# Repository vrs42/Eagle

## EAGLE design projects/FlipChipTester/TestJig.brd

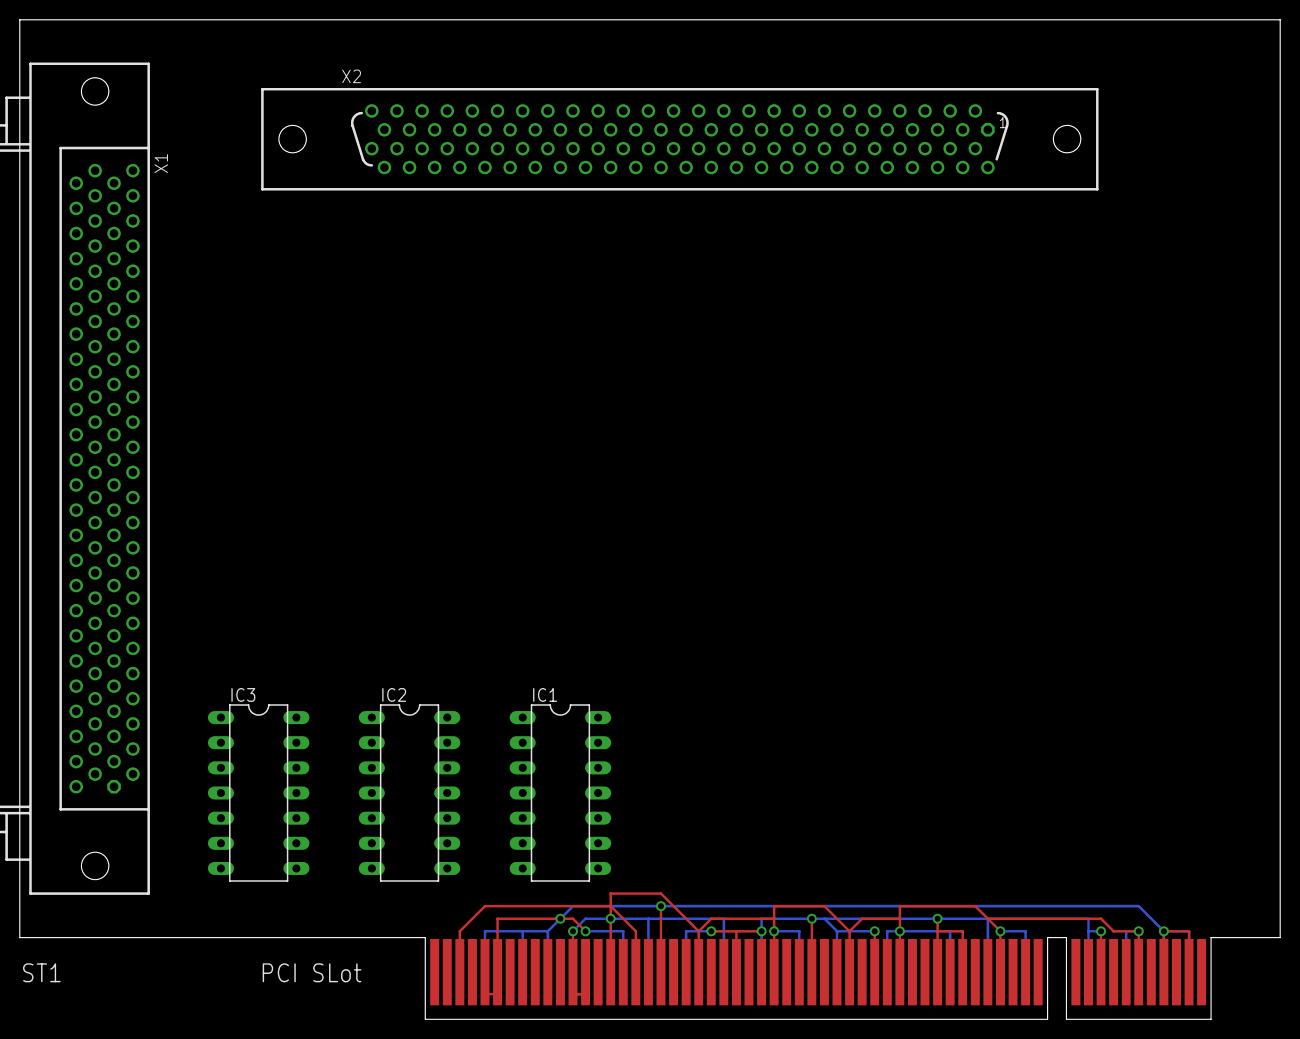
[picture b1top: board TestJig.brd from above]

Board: 2 copper layers, 127.3 x 101.0 mm, 6 parts (0 on the bottom side), 4 nets.

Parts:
IC1: 74125N; DIL14
IC2: 74126N; DIL14
IC3: 74LS63N; DIL14
ST1: PCI_BRD
X1: HFR100RA
X2: HXR100ST

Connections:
+3,3V: ST1.C25, ST1.C31, ST1.C36, ST1.C41, ST1.C43, ST1.C54, ST1.S21, ST1.S27, ST1.S33, ST1.S45, ST1.S53
+5V: ST1.C5, ST1.C6, ST1.C19, ST1.C59, ST1.C61, ST1.C62, ST1.S5, ST1.S8, ST1.S10, ST1.S16, ST1.S59, ST1.S61, ST1.S62
GND: IC1.7, IC2.7, IC3.7, ST1.C3, ST1.C12, ST1.C13, ST1.C15, ST1.C17, ST1.C22, ST1.C28, ST1.C34, ST1.C38, ST1.C46, ST1.C49, ST1.C57, ST1.S12, ST1.S13, ST1.S18, ST1.S24, ST1.S30, ST1.S37, ST1.S42, ST1.S48, ST1.S56
VCC: IC1.14, IC2.14, IC3.14

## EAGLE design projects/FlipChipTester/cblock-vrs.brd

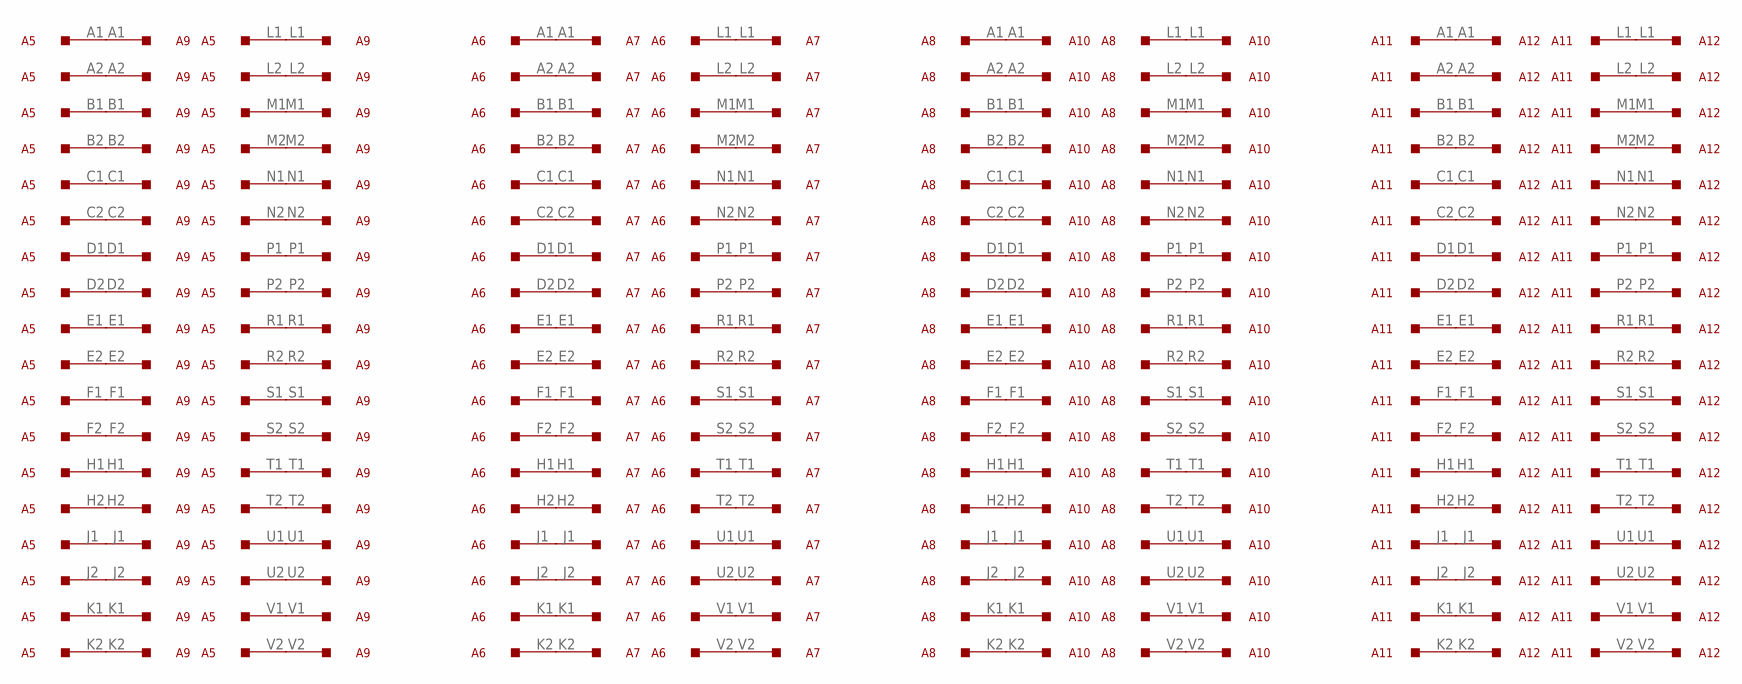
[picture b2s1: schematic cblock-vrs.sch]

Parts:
A5, A6, A7, A8, A9, A10, A11, A12: M916; H807

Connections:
unnamed: A5.L1, A9.L1
unnamed: A5.L2, A9.L2
unnamed: A5.M1, A9.M1
unnamed: A5.M2, A9.M2
unnamed: A5.N1, A9.N1
unnamed: A5.N2, A9.N2
unnamed: A5.P1, A9.P1
unnamed: A5.P2, A9.P2
unnamed: A5.R1, A9.R1
unnamed: A5.R2, A9.R2
unnamed: A5.S1, A9.S1
unnamed: A5.S2, A9.S2
unnamed: A5.T1, A9.T1
unnamed: A5.T2, A9.T2
unnamed: A5.U1, A9.U1
unnamed: A5.U2, A9.U2
unnamed: A5.V1, A9.V1
unnamed: A5.V2, A9.V2
unnamed: A5.A1, A9.A1
unnamed: A5.A2, A9.A2
unnamed: A5.B1, A9.B1
unnamed: A5.B2, A9.B2
unnamed: A5.C1, A9.C1
unnamed: A5.C2, A9.C2
unnamed: A5.D1, A9.D1
unnamed: A5.D2, A9.D2
unnamed: A5.E1, A9.E1
unnamed: A5.E2, A9.E2
unnamed: A5.F1, A9.F1
unnamed: A5.F2, A9.F2
unnamed: A5.H1, A9.H1
unnamed: A5.H2, A9.H2
unnamed: A5.J1, A9.J1
unnamed: A5.J2, A9.J2
unnamed: A5.K1, A9.K1
unnamed: A5.K2, A9.K2
unnamed: A6.L1, A7.L1
unnamed: A6.L2, A7.L2
unnamed: A6.M1, A7.M1
unnamed: A6.M2, A7.M2
unnamed: A6.N1, A7.N1
unnamed: A6.N2, A7.N2
unnamed: A6.P1, A7.P1
unnamed: A6.P2, A7.P2
unnamed: A6.R1, A7.R1
unnamed: A6.R2, A7.R2
unnamed: A6.S1, A7.S1
unnamed: A6.S2, A7.S2
unnamed: A6.T1, A7.T1
unnamed: A6.T2, A7.T2
unnamed: A6.U1, A7.U1
unnamed: A6.U2, A7.U2
unnamed: A6.V1, A7.V1
unnamed: A6.V2, A7.V2
unnamed: A6.A1, A7.A1
unnamed: A6.A2, A7.A2
unnamed: A6.B1, A7.B1
unnamed: A6.B2, A7.B2
unnamed: A6.C1, A7.C1
unnamed: A6.C2, A7.C2
unnamed: A6.D1, A7.D1
unnamed: A6.D2, A7.D2
unnamed: A6.E1, A7.E1
unnamed: A6.E2, A7.E2
unnamed: A6.F1, A7.F1
unnamed: A6.F2, A7.F2
unnamed: A6.H1, A7.H1
unnamed: A6.H2, A7.H2
unnamed: A6.J1, A7.J1
unnamed: A6.J2, A7.J2
unnamed: A6.K1, A7.K1
unnamed: A6.K2, A7.K2
unnamed: A8.L1, A10.L1
unnamed: A8.L2, A10.L2
unnamed: A8.M1, A10.M1
unnamed: A8.M2, A10.M2
unnamed: A8.N1, A10.N1
unnamed: A8.N2, A10.N2
unnamed: A8.P1, A10.P1
unnamed: A8.P2, A10.P2
unnamed: A8.R1, A10.R1
unnamed: A8.R2, A10.R2
unnamed: A8.S1, A10.S1
unnamed: A8.S2, A10.S2
unnamed: A8.T1, A10.T1
unnamed: A8.T2, A10.T2
unnamed: A8.U1, A10.U1
unnamed: A8.U2, A10.U2
unnamed: A8.V1, A10.V1
unnamed: A8.V2, A10.V2
unnamed: A8.A1, A10.A1
unnamed: A8.A2, A10.A2
unnamed: A8.B1, A10.B1
unnamed: A8.B2, A10.B2
unnamed: A8.C1, A10.C1
unnamed: A8.C2, A10.C2
unnamed: A8.D1, A10.D1
unnamed: A8.D2, A10.D2
unnamed: A8.E1, A10.E1
unnamed: A8.E2, A10.E2
unnamed: A8.F1, A10.F1
unnamed: A8.F2, A10.F2
unnamed: A8.H1, A10.H1
unnamed: A8.H2, A10.H2
unnamed: A8.J1, A10.J1
unnamed: A8.J2, A10.J2
unnamed: A8.K1, A10.K1
unnamed: A8.K2, A10.K2
unnamed: A11.L1, A12.L1
unnamed: A11.L2, A12.L2
unnamed: A11.M1, A12.M1
unnamed: A11.M2, A12.M2
unnamed: A11.N1, A12.N1
unnamed: A11.N2, A12.N2
unnamed: A11.P1, A12.P1
unnamed: A11.P2, A12.P2
unnamed: A11.R1, A12.R1
unnamed: A11.R2, A12.R2
unnamed: A11.S1, A12.S1
unnamed: A11.S2, A12.S2
unnamed: A11.T1, A12.T1
unnamed: A11.T2, A12.T2
unnamed: A11.U1, A12.U1
unnamed: A11.U2, A12.U2
unnamed: A11.V1, A12.V1
unnamed: A11.V2, A12.V2
unnamed: A11.A1, A12.A1
unnamed: A11.A2, A12.A2
unnamed: A11.B1, A12.B1
unnamed: A11.B2, A12.B2
unnamed: A11.C1, A12.C1
unnamed: A11.C2, A12.C2
unnamed: A11.D1, A12.D1
unnamed: A11.D2, A12.D2
unnamed: A11.E1, A12.E1
unnamed: A11.E2, A12.E2
unnamed: A11.F1, A12.F1
unnamed: A11.F2, A12.F2
unnamed: A11.H1, A12.H1
unnamed: A11.H2, A12.H2
unnamed: A11.J1, A12.J1
unnamed: A11.J2, A12.J2
unnamed: A11.K1, A12.K1
unnamed: A11.K2, A12.K2

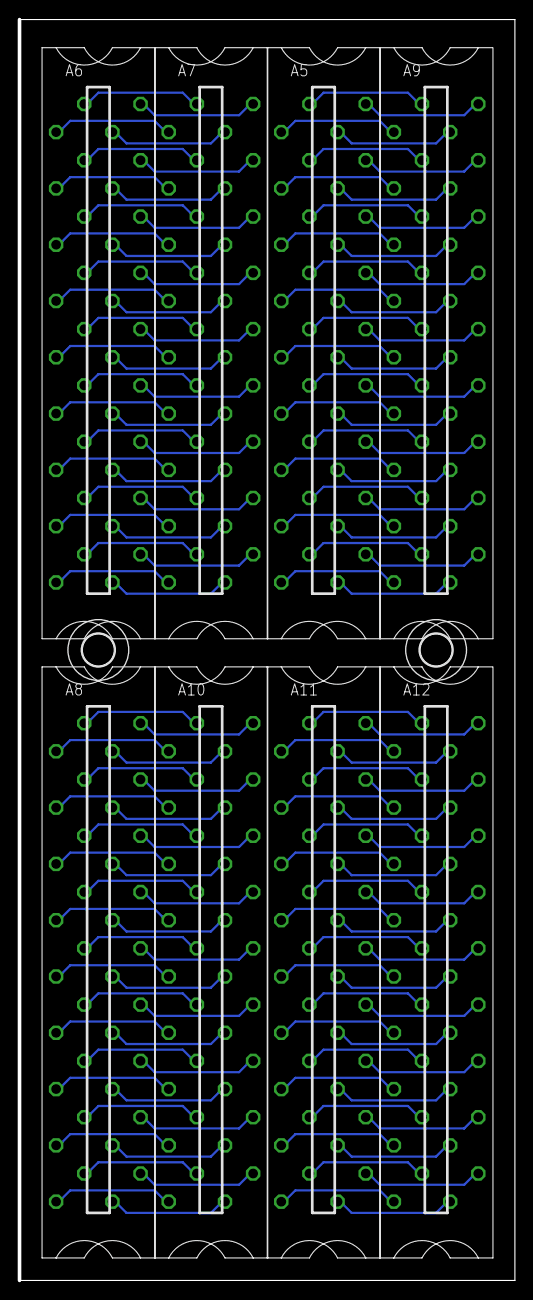
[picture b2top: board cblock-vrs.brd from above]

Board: 2 copper layers, 55.9 x 142.2 mm, 10 parts (0 on the bottom side), 144 nets.

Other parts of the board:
U$5, U$6: 3,6

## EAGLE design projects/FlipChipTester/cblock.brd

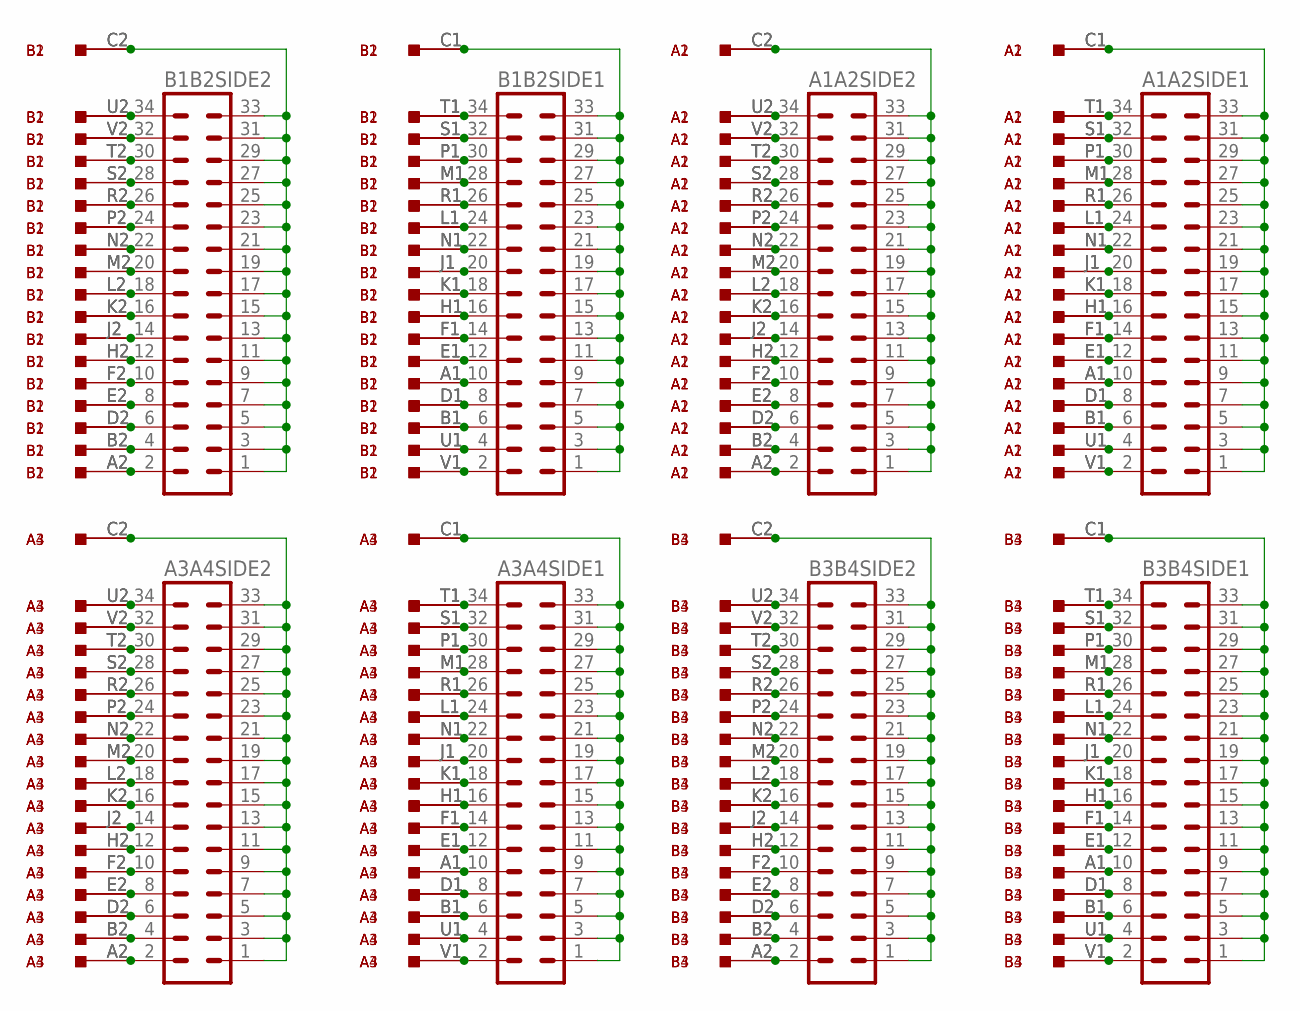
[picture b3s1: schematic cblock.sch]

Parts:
A1, A2, A3, A4: M916; H807
A1A2SIDE1, A1A2SIDE2, A3A4SIDE1, A3A4SIDE2: MA17-2
B1, B2, B3, B4: M916; H807
B1B2SIDE1, B1B2SIDE2, B3B4SIDE1, B3B4SIDE2: MA17-2

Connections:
unnamed: B1.C2, B1B2SIDE2.1, B1B2SIDE2.3, B1B2SIDE2.5, B1B2SIDE2.7, B1B2SIDE2.9, B1B2SIDE2.11, B1B2SIDE2.13, B1B2SIDE2.15, B1B2SIDE2.17, B1B2SIDE2.19, B1B2SIDE2.21, B1B2SIDE2.23, B1B2SIDE2.25, B1B2SIDE2.27, B1B2SIDE2.29, B1B2SIDE2.31, B1B2SIDE2.33, B2.C2
unnamed: B1.A2, B1B2SIDE2.2, B2.A2
unnamed: B1.B2, B1B2SIDE2.4, B2.B2
unnamed: B1.D2, B1B2SIDE2.6, B2.D2
unnamed: B1.E2, B1B2SIDE2.8, B2.E2
unnamed: B1.F2, B1B2SIDE2.10, B2.F2
unnamed: B1.H2, B1B2SIDE2.12, B2.H2
unnamed: B1.J2, B1B2SIDE2.14, B2.J2
unnamed: B1.K2, B1B2SIDE2.16, B2.K2
unnamed: B1.L2, B1B2SIDE2.18, B2.L2
unnamed: B1.M2, B1B2SIDE2.20, B2.M2
unnamed: B1.N2, B1B2SIDE2.22, B2.N2
unnamed: B1.P2, B1B2SIDE2.24, B2.P2
unnamed: B1.R2, B1B2SIDE2.26, B2.R2
unnamed: B1.S2, B1B2SIDE2.28, B2.S2
unnamed: B1.T2, B1B2SIDE2.30, B2.T2
unnamed: B1.U2, B1B2SIDE2.34, B2.U2
unnamed: B1.V2, B1B2SIDE2.32, B2.V2
unnamed: B1.A1, B1B2SIDE1.10, B2.A1
unnamed: B1.B1, B1B2SIDE1.6, B2.B1
unnamed: B1.D1, B1B2SIDE1.8, B2.D1
unnamed: B1.E1, B1B2SIDE1.12, B2.E1
unnamed: B1.F1, B1B2SIDE1.14, B2.F1
unnamed: B1.H1, B1B2SIDE1.16, B2.H1
unnamed: B1.J1, B1B2SIDE1.20, B2.J1
unnamed: B1.K1, B1B2SIDE1.18, B2.K1
unnamed: B1.L1, B1B2SIDE1.24, B2.L1
unnamed: B1.M1, B1B2SIDE1.28, B2.M1
unnamed: B1.N1, B1B2SIDE1.22, B2.N1
unnamed: B1.P1, B1B2SIDE1.30, B2.P1
unnamed: B1.R1, B1B2SIDE1.26, B2.R1
unnamed: B1.S1, B1B2SIDE1.32, B2.S1
unnamed: B1.T1, B1B2SIDE1.34, B2.T1
unnamed: B1.U1, B1B2SIDE1.4, B2.U1
unnamed: B1.V1, B1B2SIDE1.2, B2.V1
unnamed: B1.C1, B1B2SIDE1.1, B1B2SIDE1.3, B1B2SIDE1.5, B1B2SIDE1.7, B1B2SIDE1.9, B1B2SIDE1.11, B1B2SIDE1.13, B1B2SIDE1.15, B1B2SIDE1.17, B1B2SIDE1.19, B1B2SIDE1.21, B1B2SIDE1.23, B1B2SIDE1.25, B1B2SIDE1.27, B1B2SIDE1.29, B1B2SIDE1.31, B1B2SIDE1.33, B2.C1
unnamed: A1.C2, A1A2SIDE2.1, A1A2SIDE2.3, A1A2SIDE2.5, A1A2SIDE2.7, A1A2SIDE2.9, A1A2SIDE2.11, A1A2SIDE2.13, A1A2SIDE2.15, A1A2SIDE2.17, A1A2SIDE2.19, A1A2SIDE2.21, A1A2SIDE2.23, A1A2SIDE2.25, A1A2SIDE2.27, A1A2SIDE2.29, A1A2SIDE2.31, A1A2SIDE2.33, A2.C2
unnamed: A1.A2, A1A2SIDE2.2, A2.A2
unnamed: A1.B2, A1A2SIDE2.4, A2.B2
unnamed: A1.D2, A1A2SIDE2.6, A2.D2
unnamed: A1.E2, A1A2SIDE2.8, A2.E2
unnamed: A1.F2, A1A2SIDE2.10, A2.F2
unnamed: A1.H2, A1A2SIDE2.12, A2.H2
unnamed: A1.J2, A1A2SIDE2.14, A2.J2
unnamed: A1.K2, A1A2SIDE2.16, A2.K2
unnamed: A1.L2, A1A2SIDE2.18, A2.L2
unnamed: A1.M2, A1A2SIDE2.20, A2.M2
unnamed: A1.N2, A1A2SIDE2.22, A2.N2
unnamed: A1.P2, A1A2SIDE2.24, A2.P2
unnamed: A1.R2, A1A2SIDE2.26, A2.R2
unnamed: A1.S2, A1A2SIDE2.28, A2.S2
unnamed: A1.T2, A1A2SIDE2.30, A2.T2
unnamed: A1.U2, A1A2SIDE2.34, A2.U2
unnamed: A1.V2, A1A2SIDE2.32, A2.V2
unnamed: A1.A1, A1A2SIDE1.10, A2.A1
unnamed: A1.B1, A1A2SIDE1.6, A2.B1
unnamed: A1.D1, A1A2SIDE1.8, A2.D1
unnamed: A1.E1, A1A2SIDE1.12, A2.E1
unnamed: A1.F1, A1A2SIDE1.14, A2.F1
unnamed: A1.H1, A1A2SIDE1.16, A2.H1
unnamed: A1.J1, A1A2SIDE1.20, A2.J1
unnamed: A1.K1, A1A2SIDE1.18, A2.K1
unnamed: A1.L1, A1A2SIDE1.24, A2.L1
unnamed: A1.M1, A1A2SIDE1.28, A2.M1
unnamed: A1.N1, A1A2SIDE1.22, A2.N1
unnamed: A1.P1, A1A2SIDE1.30, A2.P1
unnamed: A1.R1, A1A2SIDE1.26, A2.R1
unnamed: A1.S1, A1A2SIDE1.32, A2.S1
unnamed: A1.T1, A1A2SIDE1.34, A2.T1
unnamed: A1.U1, A1A2SIDE1.4, A2.U1
unnamed: A1.V1, A1A2SIDE1.2, A2.V1
unnamed: A1.C1, A1A2SIDE1.1, A1A2SIDE1.3, A1A2SIDE1.5, A1A2SIDE1.7, A1A2SIDE1.9, A1A2SIDE1.11, A1A2SIDE1.13, A1A2SIDE1.15, A1A2SIDE1.17, A1A2SIDE1.19, A1A2SIDE1.21, A1A2SIDE1.23, A1A2SIDE1.25, A1A2SIDE1.27, A1A2SIDE1.29, A1A2SIDE1.31, A1A2SIDE1.33, A2.C1
unnamed: A3.C2, A3A4SIDE2.1, A3A4SIDE2.3, A3A4SIDE2.5, A3A4SIDE2.7, A3A4SIDE2.9, A3A4SIDE2.11, A3A4SIDE2.13, A3A4SIDE2.15, A3A4SIDE2.17, A3A4SIDE2.19, A3A4SIDE2.21, A3A4SIDE2.23, A3A4SIDE2.25, A3A4SIDE2.27, A3A4SIDE2.29, A3A4SIDE2.31, A3A4SIDE2.33, A4.C2
unnamed: A3.A2, A3A4SIDE2.2, A4.A2
unnamed: A3.B2, A3A4SIDE2.4, A4.B2
unnamed: A3.D2, A3A4SIDE2.6, A4.D2
unnamed: A3.E2, A3A4SIDE2.8, A4.E2
unnamed: A3.F2, A3A4SIDE2.10, A4.F2
unnamed: A3.H2, A3A4SIDE2.12, A4.H2
unnamed: A3.J2, A3A4SIDE2.14, A4.J2
unnamed: A3.K2, A3A4SIDE2.16, A4.K2
unnamed: A3.L2, A3A4SIDE2.18, A4.L2
unnamed: A3.M2, A3A4SIDE2.20, A4.M2
unnamed: A3.N2, A3A4SIDE2.22, A4.N2
unnamed: A3.P2, A3A4SIDE2.24, A4.P2
unnamed: A3.R2, A3A4SIDE2.26, A4.R2
unnamed: A3.S2, A3A4SIDE2.28, A4.S2
unnamed: A3.T2, A3A4SIDE2.30, A4.T2
unnamed: A3.U2, A3A4SIDE2.34, A4.U2
unnamed: A3.V2, A3A4SIDE2.32, A4.V2
unnamed: A3.A1, A3A4SIDE1.10, A4.A1
unnamed: A3.B1, A3A4SIDE1.6, A4.B1
unnamed: A3.D1, A3A4SIDE1.8, A4.D1
unnamed: A3.E1, A3A4SIDE1.12, A4.E1
unnamed: A3.F1, A3A4SIDE1.14, A4.F1
unnamed: A3.H1, A3A4SIDE1.16, A4.H1
unnamed: A3.J1, A3A4SIDE1.20, A4.J1
unnamed: A3.K1, A3A4SIDE1.18, A4.K1
unnamed: A3.L1, A3A4SIDE1.24, A4.L1
unnamed: A3.M1, A3A4SIDE1.28, A4.M1
unnamed: A3.N1, A3A4SIDE1.22, A4.N1
unnamed: A3.P1, A3A4SIDE1.30, A4.P1
unnamed: A3.R1, A3A4SIDE1.26, A4.R1
unnamed: A3.S1, A3A4SIDE1.32, A4.S1
unnamed: A3.T1, A3A4SIDE1.34, A4.T1
unnamed: A3.U1, A3A4SIDE1.4, A4.U1
unnamed: A3.V1, A3A4SIDE1.2, A4.V1
unnamed: A3.C1, A3A4SIDE1.1, A3A4SIDE1.3, A3A4SIDE1.5, A3A4SIDE1.7, A3A4SIDE1.9, A3A4SIDE1.11, A3A4SIDE1.13, A3A4SIDE1.15, A3A4SIDE1.17, A3A4SIDE1.19, A3A4SIDE1.21, A3A4SIDE1.23, A3A4SIDE1.25, A3A4SIDE1.27, A3A4SIDE1.29, A3A4SIDE1.31, A3A4SIDE1.33, A4.C1
unnamed: B3.C2, B3B4SIDE2.1, B3B4SIDE2.3, B3B4SIDE2.5, B3B4SIDE2.7, B3B4SIDE2.9, B3B4SIDE2.11, B3B4SIDE2.13, B3B4SIDE2.15, B3B4SIDE2.17, B3B4SIDE2.19, B3B4SIDE2.21, B3B4SIDE2.23, B3B4SIDE2.25, B3B4SIDE2.27, B3B4SIDE2.29, B3B4SIDE2.31, B3B4SIDE2.33, B4.C2
unnamed: B3.A2, B3B4SIDE2.2, B4.A2
unnamed: B3.B2, B3B4SIDE2.4, B4.B2
unnamed: B3.D2, B3B4SIDE2.6, B4.D2
unnamed: B3.E2, B3B4SIDE2.8, B4.E2
unnamed: B3.F2, B3B4SIDE2.10, B4.F2
unnamed: B3.H2, B3B4SIDE2.12, B4.H2
unnamed: B3.J2, B3B4SIDE2.14, B4.J2
unnamed: B3.K2, B3B4SIDE2.16, B4.K2
unnamed: B3.L2, B3B4SIDE2.18, B4.L2
unnamed: B3.M2, B3B4SIDE2.20, B4.M2
unnamed: B3.N2, B3B4SIDE2.22, B4.N2
unnamed: B3.P2, B3B4SIDE2.24, B4.P2
unnamed: B3.R2, B3B4SIDE2.26, B4.R2
unnamed: B3.S2, B3B4SIDE2.28, B4.S2
unnamed: B3.T2, B3B4SIDE2.30, B4.T2
unnamed: B3.U2, B3B4SIDE2.34, B4.U2
unnamed: B3.V2, B3B4SIDE2.32, B4.V2
unnamed: B3.A1, B3B4SIDE1.10, B4.A1
unnamed: B3.B1, B3B4SIDE1.6, B4.B1
unnamed: B3.D1, B3B4SIDE1.8, B4.D1
unnamed: B3.E1, B3B4SIDE1.12, B4.E1
unnamed: B3.F1, B3B4SIDE1.14, B4.F1
unnamed: B3.H1, B3B4SIDE1.16, B4.H1
unnamed: B3.J1, B3B4SIDE1.20, B4.J1
unnamed: B3.K1, B3B4SIDE1.18, B4.K1
unnamed: B3.L1, B3B4SIDE1.24, B4.L1
unnamed: B3.M1, B3B4SIDE1.28, B4.M1
unnamed: B3.N1, B3B4SIDE1.22, B4.N1
unnamed: B3.P1, B3B4SIDE1.30, B4.P1
unnamed: B3.R1, B3B4SIDE1.26, B4.R1
unnamed: B3.S1, B3B4SIDE1.32, B4.S1
unnamed: B3.T1, B3B4SIDE1.34, B4.T1
unnamed: B3.U1, B3B4SIDE1.4, B4.U1
unnamed: B3.V1, B3B4SIDE1.2, B4.V1
unnamed: B3.C1, B3B4SIDE1.1, B3B4SIDE1.3, B3B4SIDE1.5, B3B4SIDE1.7, B3B4SIDE1.9, B3B4SIDE1.11, B3B4SIDE1.13, B3B4SIDE1.15, B3B4SIDE1.17, B3B4SIDE1.19, B3B4SIDE1.21, B3B4SIDE1.23, B3B4SIDE1.25, B3B4SIDE1.27, B3B4SIDE1.29, B3B4SIDE1.31, B3B4SIDE1.33, B4.C1

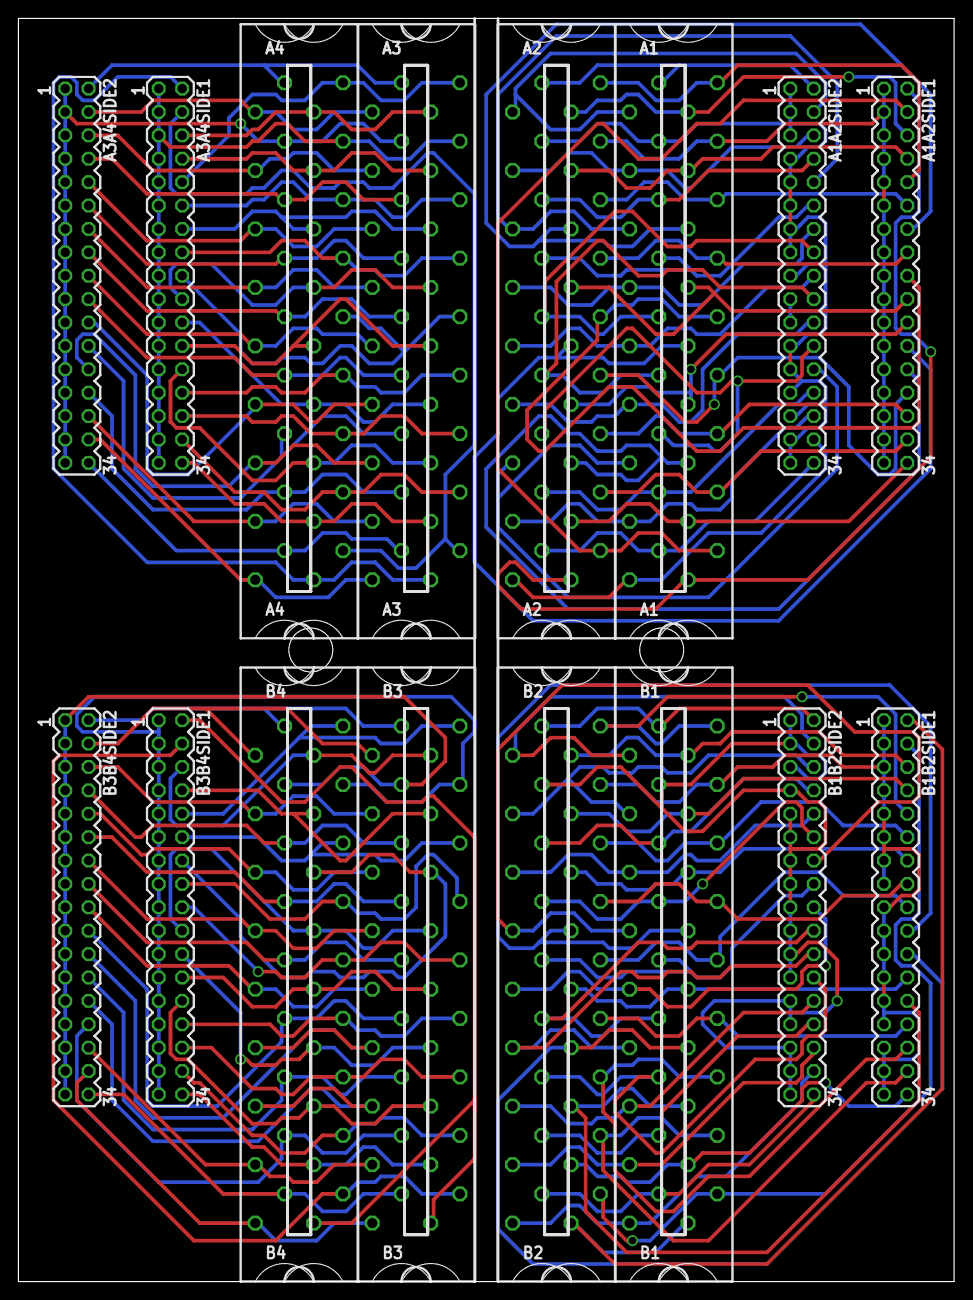
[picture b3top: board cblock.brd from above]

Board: 2 copper layers, 101.6 x 137.2 mm, 16 parts (0 on the bottom side), 144 nets.

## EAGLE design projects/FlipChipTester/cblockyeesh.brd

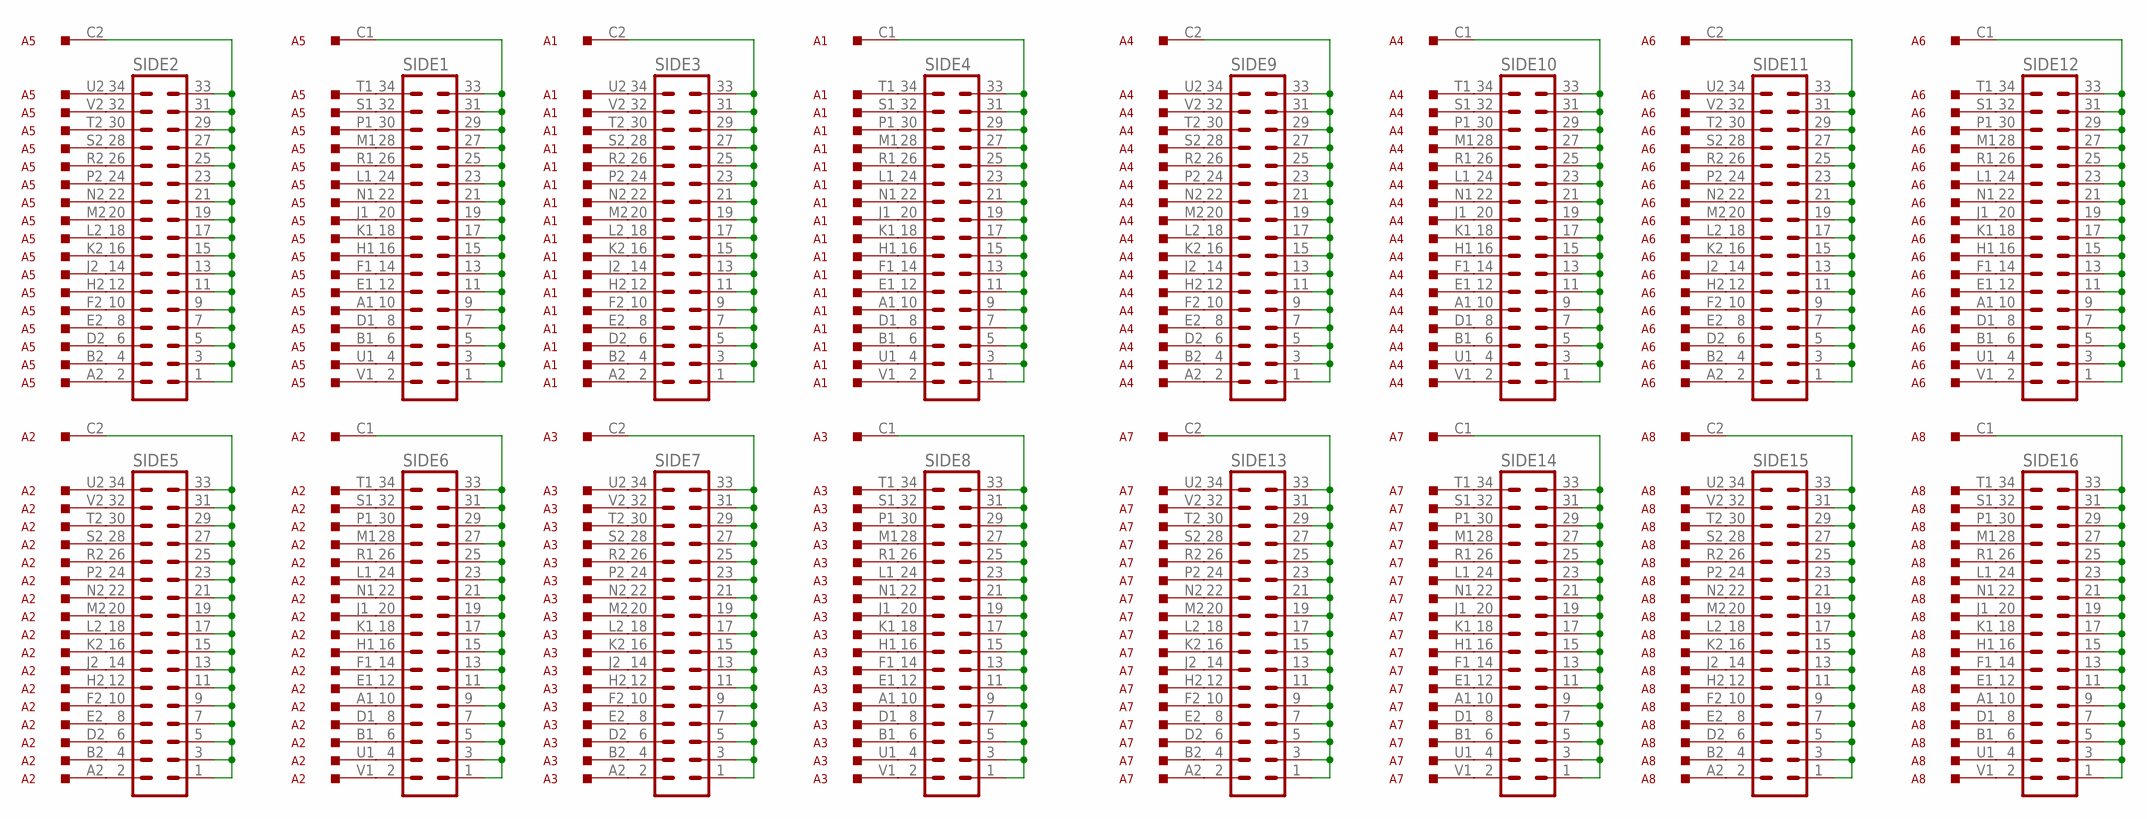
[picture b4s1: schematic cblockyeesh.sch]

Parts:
A1, A2, A3, A4, A5, A6, A7, A8: M916; H807
SIDE1, SIDE2, SIDE3, SIDE4, SIDE5, SIDE6, SIDE7, SIDE8, SIDE9, SIDE10, SIDE11, SIDE12, SIDE13, SIDE14, SIDE15, SIDE16: MA17-2

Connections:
unnamed: A5.C2, SIDE2.1, SIDE2.3, SIDE2.5, SIDE2.7, SIDE2.9, SIDE2.11, SIDE2.13, SIDE2.15, SIDE2.17, SIDE2.19, SIDE2.21, SIDE2.23, SIDE2.25, SIDE2.27, SIDE2.29, SIDE2.31, SIDE2.33
unnamed: A5.A2, SIDE2.2
unnamed: A5.B2, SIDE2.4
unnamed: A5.D2, SIDE2.6
unnamed: A5.E2, SIDE2.8
unnamed: A5.F2, SIDE2.10
unnamed: A5.H2, SIDE2.12
unnamed: A5.J2, SIDE2.14
unnamed: A5.K2, SIDE2.16
unnamed: A5.L2, SIDE2.18
unnamed: A5.M2, SIDE2.20
unnamed: A5.N2, SIDE2.22
unnamed: A5.P2, SIDE2.24
unnamed: A5.R2, SIDE2.26
unnamed: A5.S2, SIDE2.28
unnamed: A5.T2, SIDE2.30
unnamed: A5.U2, SIDE2.34
unnamed: A5.V2, SIDE2.32
unnamed: A5.A1, SIDE1.10
unnamed: A5.B1, SIDE1.6
unnamed: A5.D1, SIDE1.8
unnamed: A5.E1, SIDE1.12
unnamed: A5.F1, SIDE1.14
unnamed: A5.H1, SIDE1.16
unnamed: A5.J1, SIDE1.20
unnamed: A5.K1, SIDE1.18
unnamed: A5.L1, SIDE1.24
unnamed: A5.M1, SIDE1.28
unnamed: A5.N1, SIDE1.22
unnamed: A5.P1, SIDE1.30
unnamed: A5.R1, SIDE1.26
unnamed: A5.S1, SIDE1.32
unnamed: A5.T1, SIDE1.34
unnamed: A5.U1, SIDE1.4
unnamed: A5.V1, SIDE1.2
unnamed: A5.C1, SIDE1.1, SIDE1.3, SIDE1.5, SIDE1.7, SIDE1.9, SIDE1.11, SIDE1.13, SIDE1.15, SIDE1.17, SIDE1.19, SIDE1.21, SIDE1.23, SIDE1.25, SIDE1.27, SIDE1.29, SIDE1.31, SIDE1.33
unnamed: A1.C2, SIDE3.1, SIDE3.3, SIDE3.5, SIDE3.7, SIDE3.9, SIDE3.11, SIDE3.13, SIDE3.15, SIDE3.17, SIDE3.19, SIDE3.21, SIDE3.23, SIDE3.25, SIDE3.27, SIDE3.29, SIDE3.31, SIDE3.33
unnamed: A1.A2, SIDE3.2
unnamed: A1.B2, SIDE3.4
unnamed: A1.D2, SIDE3.6
unnamed: A1.E2, SIDE3.8
unnamed: A1.F2, SIDE3.10
unnamed: A1.H2, SIDE3.12
unnamed: A1.J2, SIDE3.14
unnamed: A1.K2, SIDE3.16
unnamed: A1.L2, SIDE3.18
unnamed: A1.M2, SIDE3.20
unnamed: A1.N2, SIDE3.22
unnamed: A1.P2, SIDE3.24
unnamed: A1.R2, SIDE3.26
unnamed: A1.S2, SIDE3.28
unnamed: A1.T2, SIDE3.30
unnamed: A1.U2, SIDE3.34
unnamed: A1.V2, SIDE3.32
unnamed: A1.A1, SIDE4.10
unnamed: A1.B1, SIDE4.6
unnamed: A1.D1, SIDE4.8
unnamed: A1.E1, SIDE4.12
unnamed: A1.F1, SIDE4.14
unnamed: A1.H1, SIDE4.16
unnamed: A1.J1, SIDE4.20
unnamed: A1.K1, SIDE4.18
unnamed: A1.L1, SIDE4.24
unnamed: A1.M1, SIDE4.28
unnamed: A1.N1, SIDE4.22
unnamed: A1.P1, SIDE4.30
unnamed: A1.R1, SIDE4.26
unnamed: A1.S1, SIDE4.32
unnamed: A1.T1, SIDE4.34
unnamed: A1.U1, SIDE4.4
unnamed: A1.V1, SIDE4.2
unnamed: A1.C1, SIDE4.1, SIDE4.3, SIDE4.5, SIDE4.7, SIDE4.9, SIDE4.11, SIDE4.13, SIDE4.15, SIDE4.17, SIDE4.19, SIDE4.21, SIDE4.23, SIDE4.25, SIDE4.27, SIDE4.29, SIDE4.31, SIDE4.33
unnamed: A2.C2, SIDE5.1, SIDE5.3, SIDE5.5, SIDE5.7, SIDE5.9, SIDE5.11, SIDE5.13, SIDE5.15, SIDE5.17, SIDE5.19, SIDE5.21, SIDE5.23, SIDE5.25, SIDE5.27, SIDE5.29, SIDE5.31, SIDE5.33
unnamed: A2.A2, SIDE5.2
unnamed: A2.B2, SIDE5.4
unnamed: A2.D2, SIDE5.6
unnamed: A2.E2, SIDE5.8
unnamed: A2.F2, SIDE5.10
unnamed: A2.H2, SIDE5.12
unnamed: A2.J2, SIDE5.14
unnamed: A2.K2, SIDE5.16
unnamed: A2.L2, SIDE5.18
unnamed: A2.M2, SIDE5.20
unnamed: A2.N2, SIDE5.22
unnamed: A2.P2, SIDE5.24
unnamed: A2.R2, SIDE5.26
unnamed: A2.S2, SIDE5.28
unnamed: A2.T2, SIDE5.30
unnamed: A2.U2, SIDE5.34
unnamed: A2.V2, SIDE5.32
unnamed: A2.A1, SIDE6.10
unnamed: A2.B1, SIDE6.6
unnamed: A2.D1, SIDE6.8
unnamed: A2.E1, SIDE6.12
unnamed: A2.F1, SIDE6.14
unnamed: A2.H1, SIDE6.16
unnamed: A2.J1, SIDE6.20
unnamed: A2.K1, SIDE6.18
unnamed: A2.L1, SIDE6.24
unnamed: A2.M1, SIDE6.28
unnamed: A2.N1, SIDE6.22
unnamed: A2.P1, SIDE6.30
unnamed: A2.R1, SIDE6.26
unnamed: A2.S1, SIDE6.32
unnamed: A2.T1, SIDE6.34
unnamed: A2.U1, SIDE6.4
unnamed: A2.V1, SIDE6.2
unnamed: A2.C1, SIDE6.1, SIDE6.3, SIDE6.5, SIDE6.7, SIDE6.9, SIDE6.11, SIDE6.13, SIDE6.15, SIDE6.17, SIDE6.19, SIDE6.21, SIDE6.23, SIDE6.25, SIDE6.27, SIDE6.29, SIDE6.31, SIDE6.33
unnamed: A3.C2, SIDE7.1, SIDE7.3, SIDE7.5, SIDE7.7, SIDE7.9, SIDE7.11, SIDE7.13, SIDE7.15, SIDE7.17, SIDE7.19, SIDE7.21, SIDE7.23, SIDE7.25, SIDE7.27, SIDE7.29, SIDE7.31, SIDE7.33
unnamed: A3.A2, SIDE7.2
unnamed: A3.B2, SIDE7.4
unnamed: A3.D2, SIDE7.6
unnamed: A3.E2, SIDE7.8
unnamed: A3.F2, SIDE7.10
unnamed: A3.H2, SIDE7.12
unnamed: A3.J2, SIDE7.14
unnamed: A3.K2, SIDE7.16
unnamed: A3.L2, SIDE7.18
unnamed: A3.M2, SIDE7.20
unnamed: A3.N2, SIDE7.22
unnamed: A3.P2, SIDE7.24
unnamed: A3.R2, SIDE7.26
unnamed: A3.S2, SIDE7.28
unnamed: A3.T2, SIDE7.30
unnamed: A3.U2, SIDE7.34
unnamed: A3.V2, SIDE7.32
unnamed: A3.A1, SIDE8.10
unnamed: A3.B1, SIDE8.6
unnamed: A3.D1, SIDE8.8
unnamed: A3.E1, SIDE8.12
unnamed: A3.F1, SIDE8.14
unnamed: A3.H1, SIDE8.16
unnamed: A3.J1, SIDE8.20
unnamed: A3.K1, SIDE8.18
unnamed: A3.L1, SIDE8.24
unnamed: A3.M1, SIDE8.28
unnamed: A3.N1, SIDE8.22
unnamed: A3.P1, SIDE8.30
unnamed: A3.R1, SIDE8.26
unnamed: A3.S1, SIDE8.32
unnamed: A3.T1, SIDE8.34
unnamed: A3.U1, SIDE8.4
unnamed: A3.V1, SIDE8.2
unnamed: A3.C1, SIDE8.1, SIDE8.3, SIDE8.5, SIDE8.7, SIDE8.9, SIDE8.11, SIDE8.13, SIDE8.15, SIDE8.17, SIDE8.19, SIDE8.21, SIDE8.23, SIDE8.25, SIDE8.27, SIDE8.29, SIDE8.31, SIDE8.33
unnamed: A4.C2, SIDE9.1, SIDE9.3, SIDE9.5, SIDE9.7, SIDE9.9, SIDE9.11, SIDE9.13, SIDE9.15, SIDE9.17, SIDE9.19, SIDE9.21, SIDE9.23, SIDE9.25, SIDE9.27, SIDE9.29, SIDE9.31, SIDE9.33
unnamed: A4.A2, SIDE9.2
unnamed: A4.B2, SIDE9.4
unnamed: A4.D2, SIDE9.6
unnamed: A4.E2, SIDE9.8
unnamed: A4.F2, SIDE9.10
unnamed: A4.H2, SIDE9.12
unnamed: A4.J2, SIDE9.14
unnamed: A4.K2, SIDE9.16
unnamed: A4.L2, SIDE9.18
unnamed: A4.M2, SIDE9.20
unnamed: A4.N2, SIDE9.22
unnamed: A4.P2, SIDE9.24
unnamed: A4.R2, SIDE9.26
unnamed: A4.S2, SIDE9.28
unnamed: A4.T2, SIDE9.30
unnamed: A4.U2, SIDE9.34
unnamed: A4.V2, SIDE9.32
unnamed: A4.A1, SIDE10.10
unnamed: A4.B1, SIDE10.6
unnamed: A4.D1, SIDE10.8
unnamed: A4.E1, SIDE10.12
unnamed: A4.F1, SIDE10.14
unnamed: A4.H1, SIDE10.16
unnamed: A4.J1, SIDE10.20
unnamed: A4.K1, SIDE10.18
unnamed: A4.L1, SIDE10.24
unnamed: A4.M1, SIDE10.28
unnamed: A4.N1, SIDE10.22
unnamed: A4.P1, SIDE10.30
unnamed: A4.R1, SIDE10.26
unnamed: A4.S1, SIDE10.32
unnamed: A4.T1, SIDE10.34
unnamed: A4.U1, SIDE10.4
unnamed: A4.V1, SIDE10.2
unnamed: A4.C1, SIDE10.1, SIDE10.3, SIDE10.5, SIDE10.7, SIDE10.9, SIDE10.11, SIDE10.13, SIDE10.15, SIDE10.17, SIDE10.19, SIDE10.21, SIDE10.23, SIDE10.25, SIDE10.27, SIDE10.29, SIDE10.31, SIDE10.33
unnamed: A6.C2, SIDE11.1, SIDE11.3, SIDE11.5, SIDE11.7, SIDE11.9, SIDE11.11, SIDE11.13, SIDE11.15, SIDE11.17, SIDE11.19, SIDE11.21, SIDE11.23, SIDE11.25, SIDE11.27, SIDE11.29, SIDE11.31, SIDE11.33
unnamed: A6.A2, SIDE11.2
unnamed: A6.B2, SIDE11.4
unnamed: A6.D2, SIDE11.6
unnamed: A6.E2, SIDE11.8
unnamed: A6.F2, SIDE11.10
unnamed: A6.H2, SIDE11.12
unnamed: A6.J2, SIDE11.14
unnamed: A6.K2, SIDE11.16
unnamed: A6.L2, SIDE11.18
unnamed: A6.M2, SIDE11.20
unnamed: A6.N2, SIDE11.22
unnamed: A6.P2, SIDE11.24
unnamed: A6.R2, SIDE11.26
unnamed: A6.S2, SIDE11.28
unnamed: A6.T2, SIDE11.30
unnamed: A6.U2, SIDE11.34
unnamed: A6.V2, SIDE11.32
unnamed: A6.A1, SIDE12.10
unnamed: A6.B1, SIDE12.6
unnamed: A6.D1, SIDE12.8
unnamed: A6.E1, SIDE12.12
unnamed: A6.F1, SIDE12.14
unnamed: A6.H1, SIDE12.16
unnamed: A6.J1, SIDE12.20
unnamed: A6.K1, SIDE12.18
unnamed: A6.L1, SIDE12.24
unnamed: A6.M1, SIDE12.28
unnamed: A6.N1, SIDE12.22
unnamed: A6.P1, SIDE12.30
unnamed: A6.R1, SIDE12.26
unnamed: A6.S1, SIDE12.32
unnamed: A6.T1, SIDE12.34
unnamed: A6.U1, SIDE12.4
unnamed: A6.V1, SIDE12.2
unnamed: A6.C1, SIDE12.1, SIDE12.3, SIDE12.5, SIDE12.7, SIDE12.9, SIDE12.11, SIDE12.13, SIDE12.15, SIDE12.17, SIDE12.19, SIDE12.21, SIDE12.23, SIDE12.25, SIDE12.27, SIDE12.29, SIDE12.31, SIDE12.33
unnamed: A7.C2, SIDE13.1, SIDE13.3, SIDE13.5, SIDE13.7, SIDE13.9, SIDE13.11, SIDE13.13, SIDE13.15, SIDE13.17, SIDE13.19, SIDE13.21, SIDE13.23, SIDE13.25, SIDE13.27, SIDE13.29, SIDE13.31, SIDE13.33
unnamed: A7.A2, SIDE13.2
unnamed: A7.B2, SIDE13.4
unnamed: A7.D2, SIDE13.6
unnamed: A7.E2, SIDE13.8
unnamed: A7.F2, SIDE13.10
unnamed: A7.H2, SIDE13.12
unnamed: A7.J2, SIDE13.14
unnamed: A7.K2, SIDE13.16
unnamed: A7.L2, SIDE13.18
unnamed: A7.M2, SIDE13.20
unnamed: A7.N2, SIDE13.22
unnamed: A7.P2, SIDE13.24
unnamed: A7.R2, SIDE13.26
unnamed: A7.S2, SIDE13.28
unnamed: A7.T2, SIDE13.30
unnamed: A7.U2, SIDE13.34
unnamed: A7.V2, SIDE13.32
unnamed: A7.A1, SIDE14.10
unnamed: A7.B1, SIDE14.6
unnamed: A7.D1, SIDE14.8
unnamed: A7.E1, SIDE14.12
unnamed: A7.F1, SIDE14.14
unnamed: A7.H1, SIDE14.16
unnamed: A7.J1, SIDE14.20
unnamed: A7.K1, SIDE14.18
unnamed: A7.L1, SIDE14.24
unnamed: A7.M1, SIDE14.28
unnamed: A7.N1, SIDE14.22
unnamed: A7.P1, SIDE14.30
unnamed: A7.R1, SIDE14.26
unnamed: A7.S1, SIDE14.32
unnamed: A7.T1, SIDE14.34
unnamed: A7.U1, SIDE14.4
unnamed: A7.V1, SIDE14.2
unnamed: A7.C1, SIDE14.1, SIDE14.3, SIDE14.5, SIDE14.7, SIDE14.9, SIDE14.11, SIDE14.13, SIDE14.15, SIDE14.17, SIDE14.19, SIDE14.21, SIDE14.23, SIDE14.25, SIDE14.27, SIDE14.29, SIDE14.31, SIDE14.33
unnamed: A8.C2, SIDE15.1, SIDE15.3, SIDE15.5, SIDE15.7, SIDE15.9, SIDE15.11, SIDE15.13, SIDE15.15, SIDE15.17, SIDE15.19, SIDE15.21, SIDE15.23, SIDE15.25, SIDE15.27, SIDE15.29, SIDE15.31, SIDE15.33
unnamed: A8.A2, SIDE15.2
unnamed: A8.B2, SIDE15.4
unnamed: A8.D2, SIDE15.6
unnamed: A8.E2, SIDE15.8
unnamed: A8.F2, SIDE15.10
unnamed: A8.H2, SIDE15.12
unnamed: A8.J2, SIDE15.14
unnamed: A8.K2, SIDE15.16
unnamed: A8.L2, SIDE15.18
unnamed: A8.M2, SIDE15.20
unnamed: A8.N2, SIDE15.22
unnamed: A8.P2, SIDE15.24
unnamed: A8.R2, SIDE15.26
unnamed: A8.S2, SIDE15.28
unnamed: A8.T2, SIDE15.30
unnamed: A8.U2, SIDE15.34
unnamed: A8.V2, SIDE15.32
unnamed: A8.A1, SIDE16.10
unnamed: A8.B1, SIDE16.6
unnamed: A8.D1, SIDE16.8
unnamed: A8.E1, SIDE16.12
unnamed: A8.F1, SIDE16.14
unnamed: A8.H1, SIDE16.16
unnamed: A8.J1, SIDE16.20
unnamed: A8.K1, SIDE16.18
unnamed: A8.L1, SIDE16.24
unnamed: A8.M1, SIDE16.28
unnamed: A8.N1, SIDE16.22
unnamed: A8.P1, SIDE16.30
unnamed: A8.R1, SIDE16.26
unnamed: A8.S1, SIDE16.32
unnamed: A8.T1, SIDE16.34
unnamed: A8.U1, SIDE16.4
unnamed: A8.V1, SIDE16.2
unnamed: A8.C1, SIDE16.1, SIDE16.3, SIDE16.5, SIDE16.7, SIDE16.9, SIDE16.11, SIDE16.13, SIDE16.15, SIDE16.17, SIDE16.19, SIDE16.21, SIDE16.23, SIDE16.25, SIDE16.27, SIDE16.29, SIDE16.31, SIDE16.33

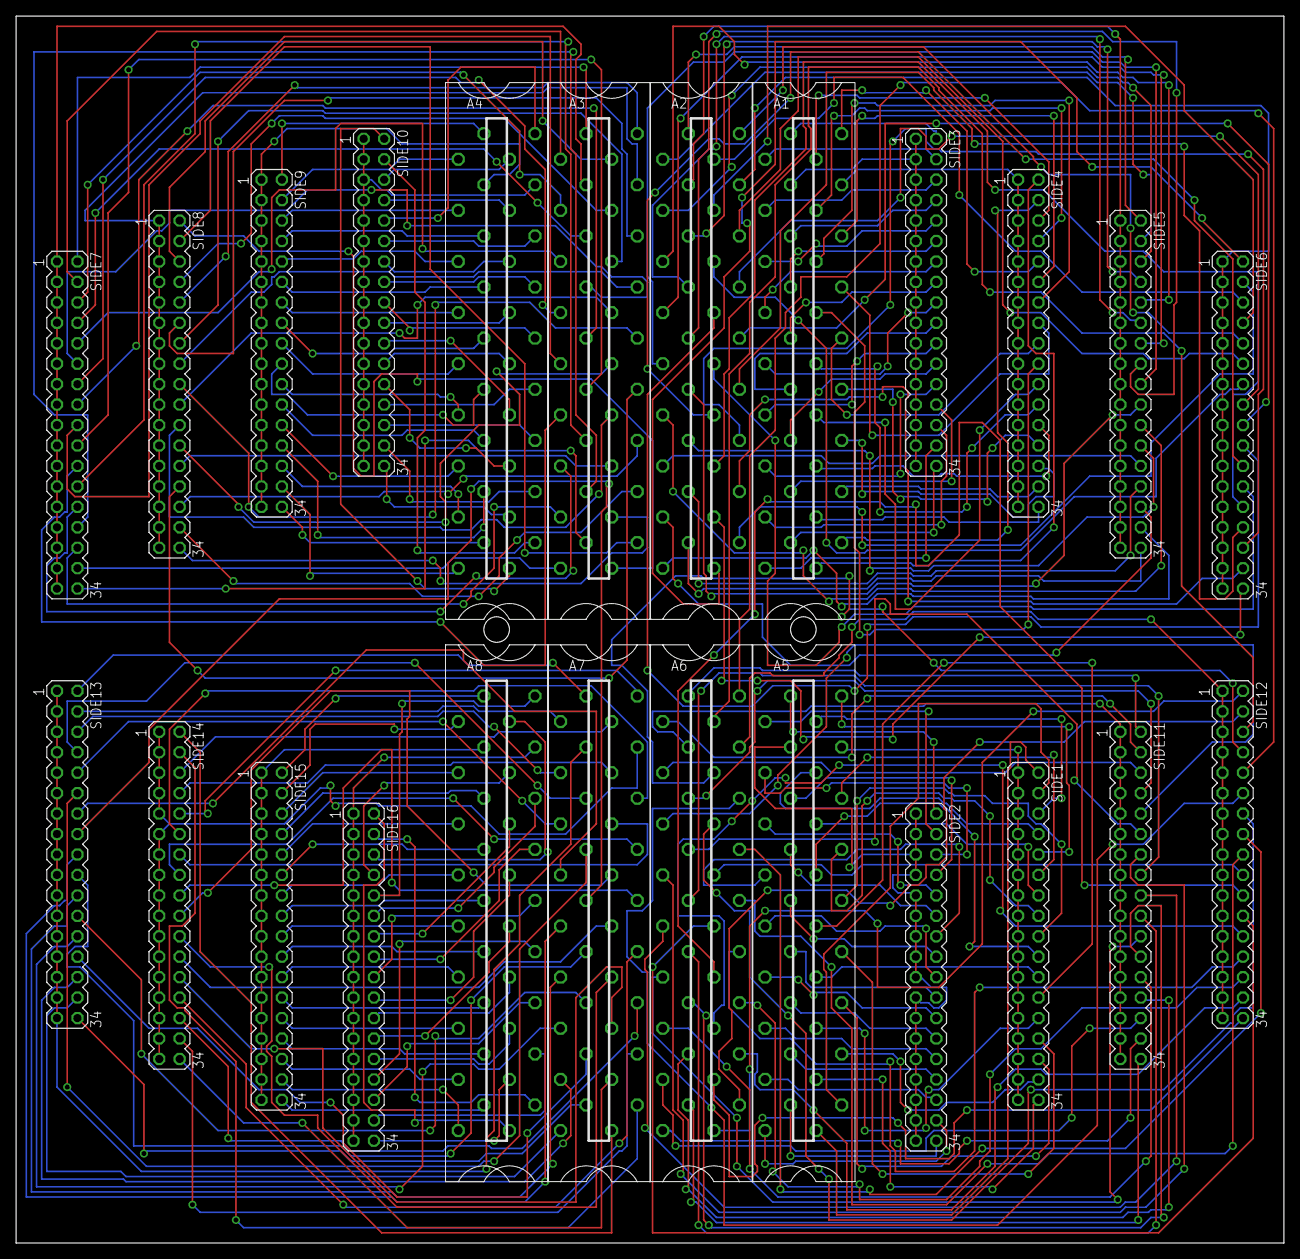
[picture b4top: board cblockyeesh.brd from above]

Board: 2 copper layers, 157.5 x 152.4 mm, 24 parts (0 on the bottom side), 288 nets.
